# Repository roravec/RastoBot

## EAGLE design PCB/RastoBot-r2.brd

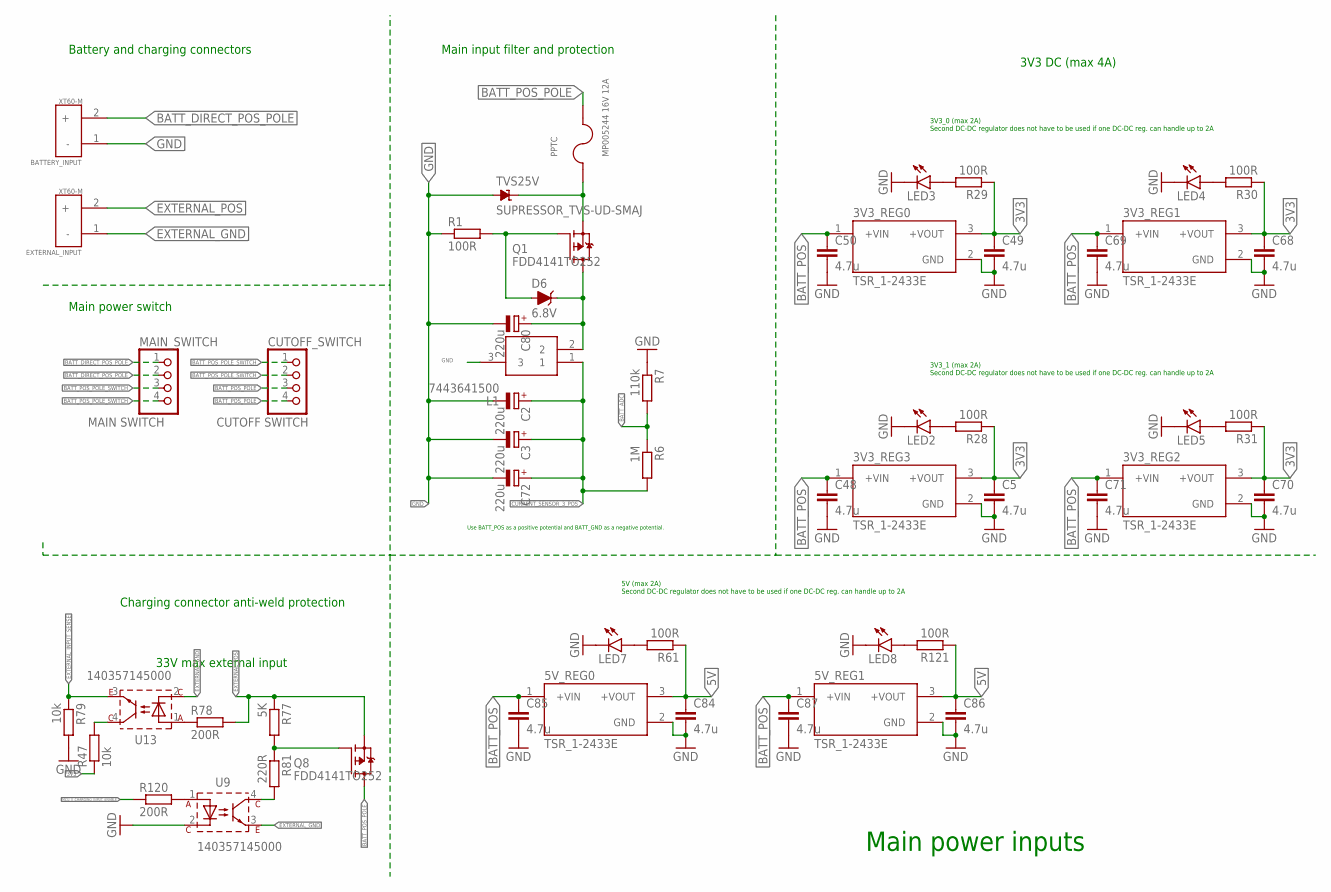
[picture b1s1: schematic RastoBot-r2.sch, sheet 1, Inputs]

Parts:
3V3_REG0, 3V3_REG1, 3V3_REG2, 3V3_REG3, 5V_REG0, 5V_REG1: TSR_1-2433E; CONV_TSR_1-2433E
BATTERY_INPUT: XT60-M; AMASS_XT60-M
C2, C3, C72, C80: 220u; E2,5-5
C5, C48, C49, C50, C68, C69, C70, C71, C84, C85, C86, C87: 4.7u; C1206
CUTOFF_SWITCH: CUTOFF SWITCH; 1X04
D6: 6.8V; SOD-323
EXTERNAL_INPUT: XT60-M; AMASS_XT60-M
L1: 7443641500; 74436413300
LED2, LED3, LED4, LED5, LED7, LED8: LEDSML0805; SML0805
MAIN_SWITCH: MAIN SWITCH; 1X04
PPTC: MP005244 16V 12A; FUSE_0ZCF0075AF2C
Q1, Q8: FDD4141TO252; TO252
R1: 100R; R0805
R6: 1M; R0805
R7: 110k; R0805
R28, R29, R30, R31, R61, R121: 100R; R0603
R47, R79: 10k; R0805
R77: 5K; R0805
R78, R120: 200R; R0805
R81: 220R; R0805
TVS25V: SUPRESSOR_TVS-UD-SMAJ; SUPRESSOR_SMAJ
U9, U13: 140357145000; WL-OCPT_SOP4

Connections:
3V3: 3V3_REG0.3 (+VOUT), 3V3_REG1.3 (+VOUT), 3V3_REG2.3 (+VOUT), 3V3_REG3.3 (+VOUT), C5.1, C49.1, C68.1, C70.1, R28.1, R29.1, R30.1, R31.1, R47.1; also elsewhere on the board
5V: 5V_REG0.3 (+VOUT), 5V_REG1.3 (+VOUT), C84.1, C86.1, R61.1, R121.1; also elsewhere on the board
BATT_ADC: R6.1, R7.2; also elsewhere on the board
BATT_DIRECT_POS_POLE: BATTERY_INPUT.2 (+), MAIN_SWITCH.1, MAIN_SWITCH.2; also elsewhere on the board
BATT_POS: 3V3_REG0.1 (+VIN), 3V3_REG1.1 (+VIN), 3V3_REG2.1 (+VIN), 3V3_REG3.1 (+VIN), 5V_REG0.1 (+VIN), 5V_REG1.1 (+VIN), C48.1, C50.1, C69.1, C71.1, C85.1, C87.1; also elsewhere on the board
BATT_POS_POLE: CUTOFF_SWITCH.3, CUTOFF_SWITCH.4, PPTC.2, Q8.3 (D)
BATT_POS_POLE_SWITCH: CUTOFF_SWITCH.1, CUTOFF_SWITCH.2, MAIN_SWITCH.3, MAIN_SWITCH.4
CURRENT_SENSOR_3_POS: C2.+, C3.+, C72.+, L1.1, R6.2; also elsewhere on the board
EXTERNAL_GND: EXTERNAL_INPUT.1 (-), U9.3, U13.2
EXTERNAL_INPUT_SENSE: R79.1, U13.3; also elsewhere on the board
EXTERNAL_POS: EXTERNAL_INPUT.2 (+), Q8.2 (S), R77.1, R78.2
GND: 3V3_REG0.2 (GND), 3V3_REG1.2 (GND), 3V3_REG2.2 (GND), 3V3_REG3.2 (GND), 5V_REG0.2 (GND), 5V_REG1.2 (GND), BATTERY_INPUT.1 (-), C2.-, C3.-, C5.2, C48.2, C49.2, C50.2, C68.2, C69.2, C70.2, C71.2, C72.-, C80.-, C84.2, C85.2, C86.2, C87.2, L1.3, LED2.C, LED3.C, LED4.C, LED5.C, LED7.C, LED8.C, R1.1, R7.1, R79.2, TVS25V.A, U9.2; also elsewhere on the board
MCU_0_CHARGING_INPUT_ENABLE: R120.1; also elsewhere on the board
unnamed: D6.A, Q1.1 (G), R1.2
unnamed: C80.+, D6.C, L1.2, Q1.3 (D)
unnamed: PPTC.1, Q1.2 (S), TVS25V.C
unnamed: LED2.A, R28.2
unnamed: LED3.A, R29.2
unnamed: LED4.A, R30.2
unnamed: LED5.A, R31.2
unnamed: R120.2, U9.1
unnamed: Q8.1 (G), R77.2, R81.1
unnamed: R81.2, U9.4
unnamed: R47.2, U13.4
unnamed: LED7.A, R61.2
unnamed: LED8.A, R121.2
unnamed: R78.1, U13.1

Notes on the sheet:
33V max external input
Charging connector anti-weld protection
Use BATT_POS as a positive potential and BATT_GND as a negative potential.
Main power inputs
3V3 DC (max 4A)
3V3_0 (max 2A) Second DC-DC regulator does not have to be used if one DC-DC reg. can handle up to 2A
3V3_1 (max 2A) Second DC-DC regulator does not have to be used if one DC-DC reg. can handle up to 2A
Main input filter and protection
Battery and charging connectors
Main power switch
5V (max 2A) Second DC-DC regulator does not have to be used if one DC-DC reg. can handle up to 2A

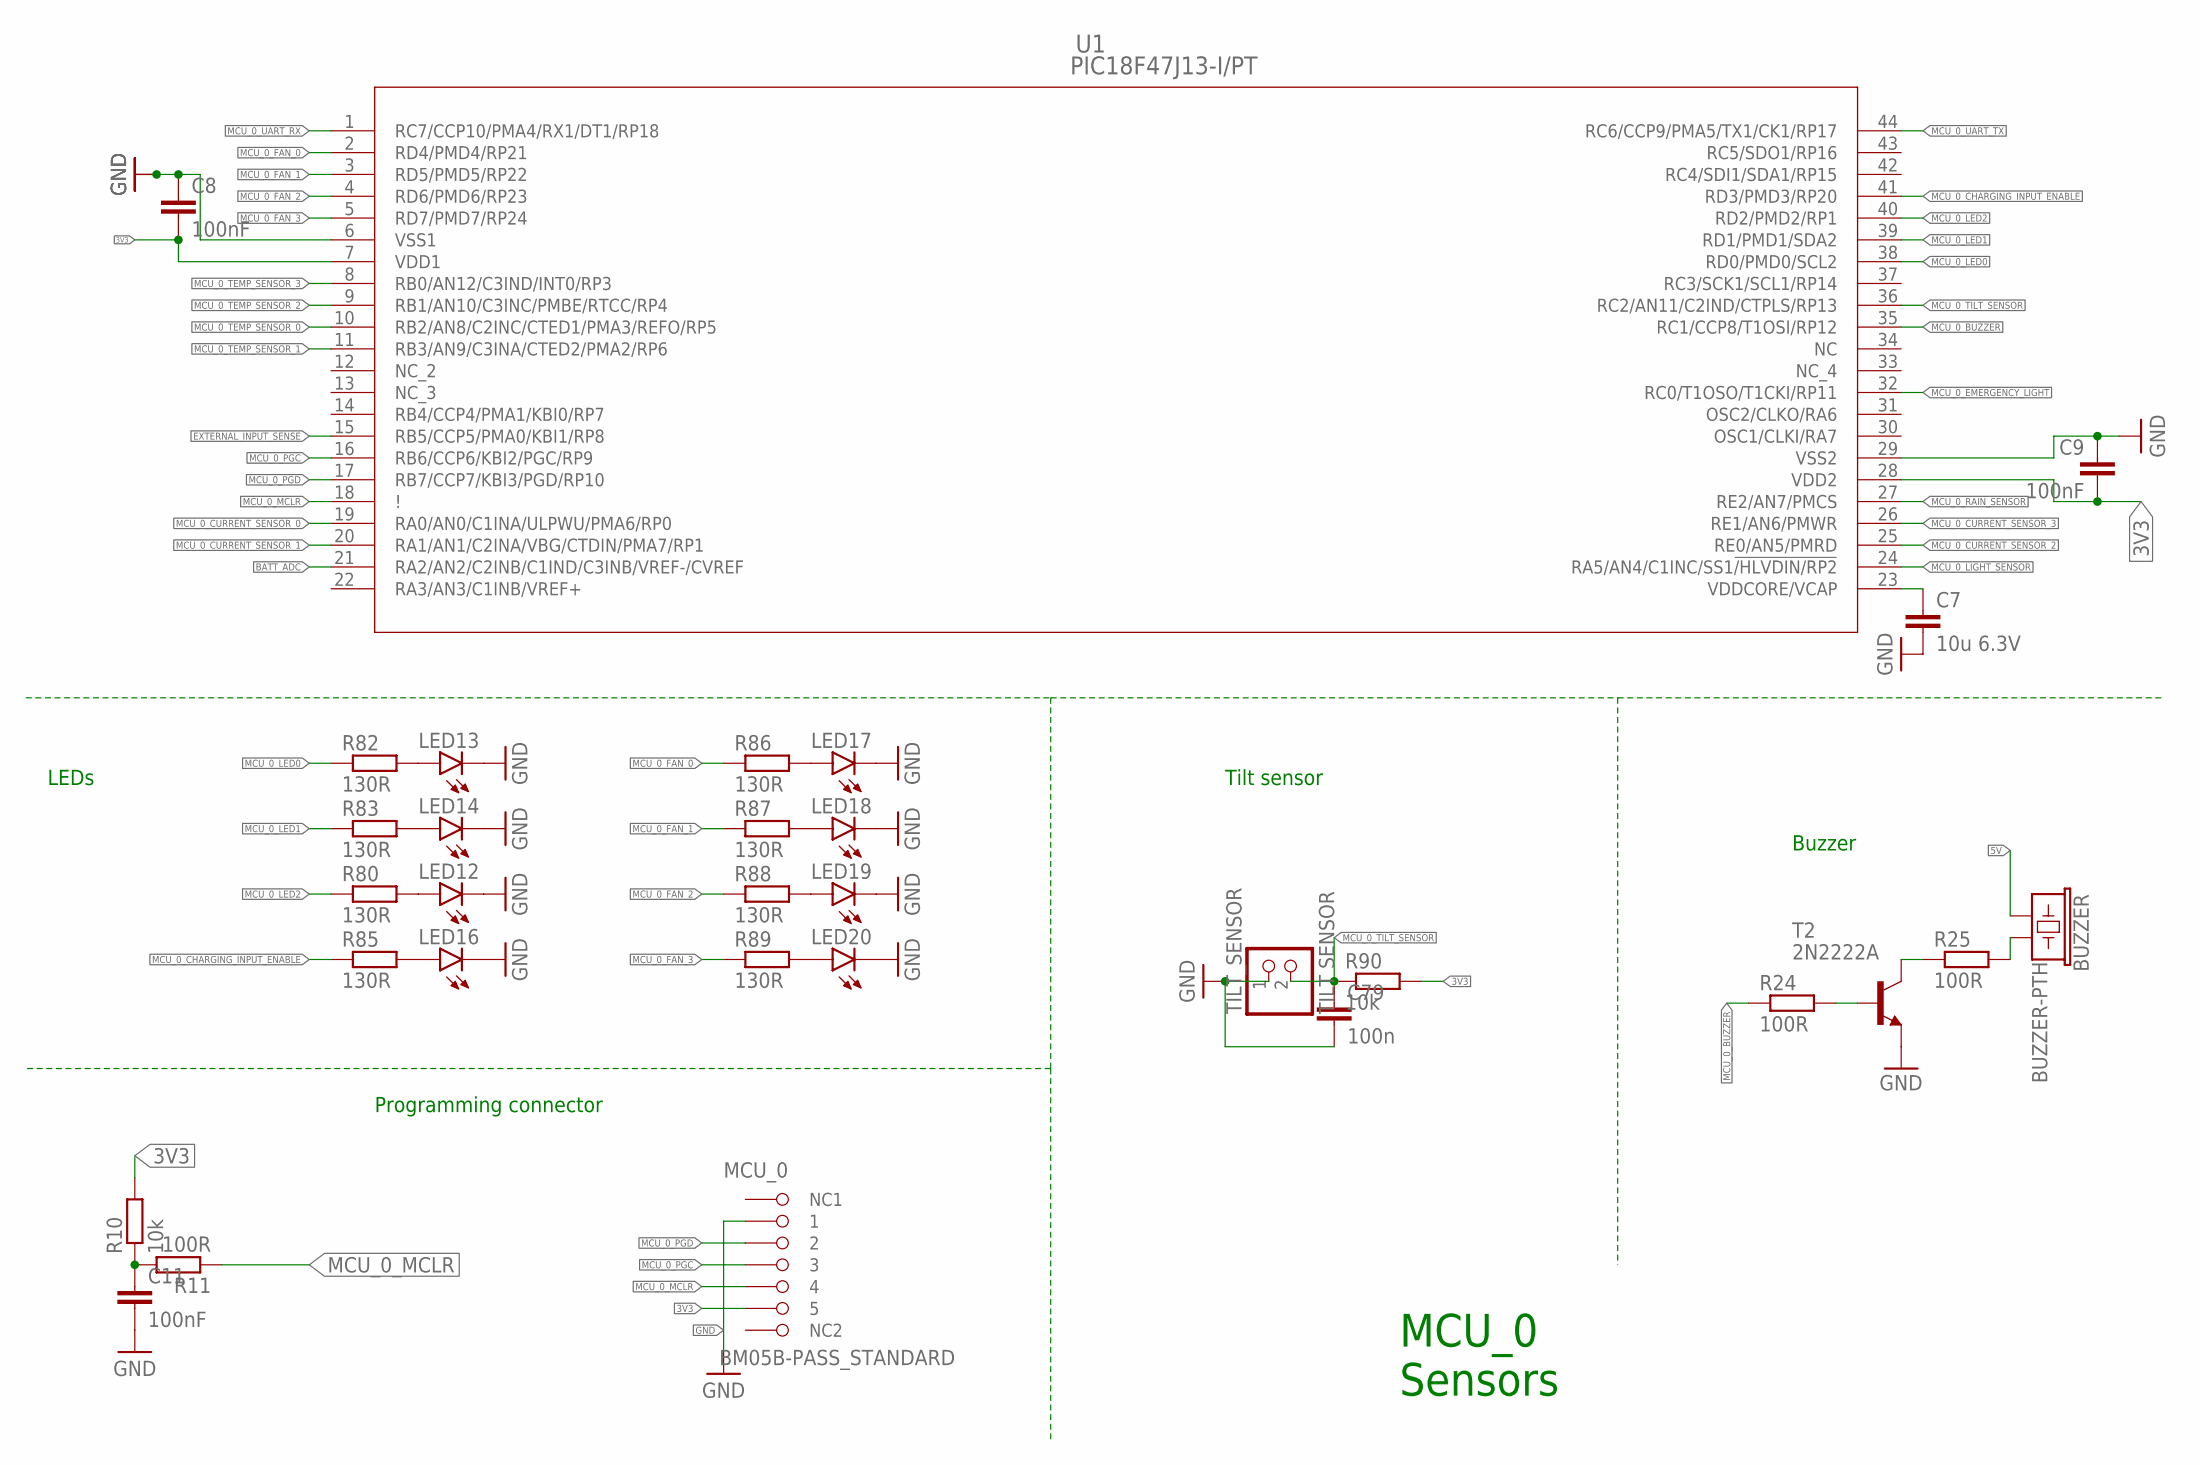
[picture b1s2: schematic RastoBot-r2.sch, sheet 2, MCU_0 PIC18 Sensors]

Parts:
BUZZER: BUZZER-PTH; BUZZER-12MM
C7: 10u 6.3V; C1206
C8, C9, C11: 100nF; C0603
C79: 100n; C1206
LED12, LED13, LED14, LED16, LED17, LED18, LED19, LED20: LEDSML0805; SML0805
MCU_0: BM05B-PASS_STANDARD; BM05B-PASS
R10: 10k; R0805
R11, R24, R25: 100R; R0805
R80, R82, R83, R85, R86, R87, R88, R89: 130R; R0603
R90: 10k; R0603
T2: 2N2222A; TO92-CBE
TILT_SENSOR: TILT SENSOR; 1X02
U1: PIC18F47J13-I/PT; TQFP44_10X10MC_MCH

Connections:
3V3: C8.2, C9.2, MCU_0.P$5 (5), R10.2, R90.2, U1.7 (VDD1), U1.28 (VDD2); also elsewhere on the board
5V: BUZZER.+ (1); also elsewhere on the board
BATT_ADC: U1.21 (RA2/AN2/C2INB/C1IND/C3INB/VREF-/CVREF); also elsewhere on the board
EXTERNAL_INPUT_SENSE: U1.15 (RB5/CCP5/PMA0/KBI1/RP8); also elsewhere on the board
GND: C7.2, C8.1, C9.1, C11.2, C79.2, LED12.C, LED13.C, LED14.C, LED16.C, LED17.C, LED18.C, LED19.C, LED20.C, MCU_0.P$1 (1), T2.E, TILT_SENSOR.1, U1.6 (VSS1), U1.29 (VSS2); also elsewhere on the board
MCU_0_BUZZER: R24.1, U1.35 (RC1/CCP8/T1OSI/RP12)
MCU_0_CHARGING_INPUT_ENABLE: R85.1, U1.41 (RD3/PMD3/RP20); also elsewhere on the board
MCU_0_CURRENT_SENSOR_0: U1.19 (RA0/AN0/C1INA/ULPWU/PMA6/RP0); also elsewhere on the board
MCU_0_CURRENT_SENSOR_1: U1.20 (RA1/AN1/C2INA/VBG/CTDIN/PMA7/RP1); also elsewhere on the board
MCU_0_CURRENT_SENSOR_2: U1.25 (RE0/AN5/PMRD); also elsewhere on the board
MCU_0_CURRENT_SENSOR_3: U1.26 (RE1/AN6/PMWR); also elsewhere on the board
MCU_0_EMERGENCY_LIGHT: U1.32 (RC0/T1OSO/T1CKI/RP11); also elsewhere on the board
MCU_0_FAN_0: R86.1, U1.2 (RD4/PMD4/RP21); also elsewhere on the board
MCU_0_FAN_1: R87.1, U1.3 (RD5/PMD5/RP22); also elsewhere on the board
MCU_0_FAN_2: R88.1, U1.4 (RD6/PMD6/RP23); also elsewhere on the board
MCU_0_FAN_3: R89.1, U1.5 (RD7/PMD7/RP24); also elsewhere on the board
MCU_0_LED0: R82.1, U1.38 (RD0/PMD0/SCL2)
MCU_0_LED1: R83.1, U1.39 (RD1/PMD1/SDA2)
MCU_0_LED2: R80.1, U1.40 (RD2/PMD2/RP1)
MCU_0_LIGHT_SENSOR: U1.24 (RA5/AN4/C1INC/SS1!/HLVDIN/RP2); also elsewhere on the board
MCU_0_MCLR: MCU_0.P$4 (4), R11.1, U1.18 (!)
MCU_0_PGC: MCU_0.P$3 (3), U1.16 (RB6/CCP6/KBI2/PGC/RP9)
MCU_0_PGD: MCU_0.P$2 (2), U1.17 (RB7/CCP7/KBI3/PGD/RP10)
MCU_0_RAIN_SENSOR: U1.27 (RE2/AN7/PMCS); also elsewhere on the board
MCU_0_TEMP_SENSOR_0: U1.10 (RB2/AN8/C2INC/CTED1/PMA3/REFO/RP5); also elsewhere on the board
MCU_0_TEMP_SENSOR_1: U1.11 (RB3/AN9/C3INA/CTED2/PMA2/RP6); also elsewhere on the board
MCU_0_TEMP_SENSOR_2: U1.9 (RB1/AN10/C3INC/PMBE/RTCC/RP4); also elsewhere on the board
MCU_0_TEMP_SENSOR_3: U1.8 (RB0/AN12/C3IND/INT0/RP3); also elsewhere on the board
MCU_0_TILT_SENSOR: C79.1, R90.1, TILT_SENSOR.2, U1.36 (RC2/AN11/C2IND/CTPLS/RP13); also elsewhere on the board
MCU_0_UART_RX: U1.1 (RC7/CCP10/PMA4/RX1/DT1/RP18); also elsewhere on the board
MCU_0_UART_TX: U1.44 (RC6/CCP9/PMA5/TX1/CK1/RP17); also elsewhere on the board
unnamed: C7.1, U1.23 (VDDCORE/VCAP)
unnamed: C11.1, R10.1, R11.2
unnamed: R24.2, T2.B
unnamed: BUZZER.- (2), R25.2
unnamed: R25.1, T2.C
unnamed: LED12.A, R80.2
unnamed: LED13.A, R82.2
unnamed: LED14.A, R83.2
unnamed: LED16.A, R85.2
unnamed: LED17.A, R86.2
unnamed: LED18.A, R87.2
unnamed: LED19.A, R88.2
unnamed: LED20.A, R89.2

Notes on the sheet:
Buzzer
MCU_0 Sensors
Tilt sensor
LEDs
Programming connector

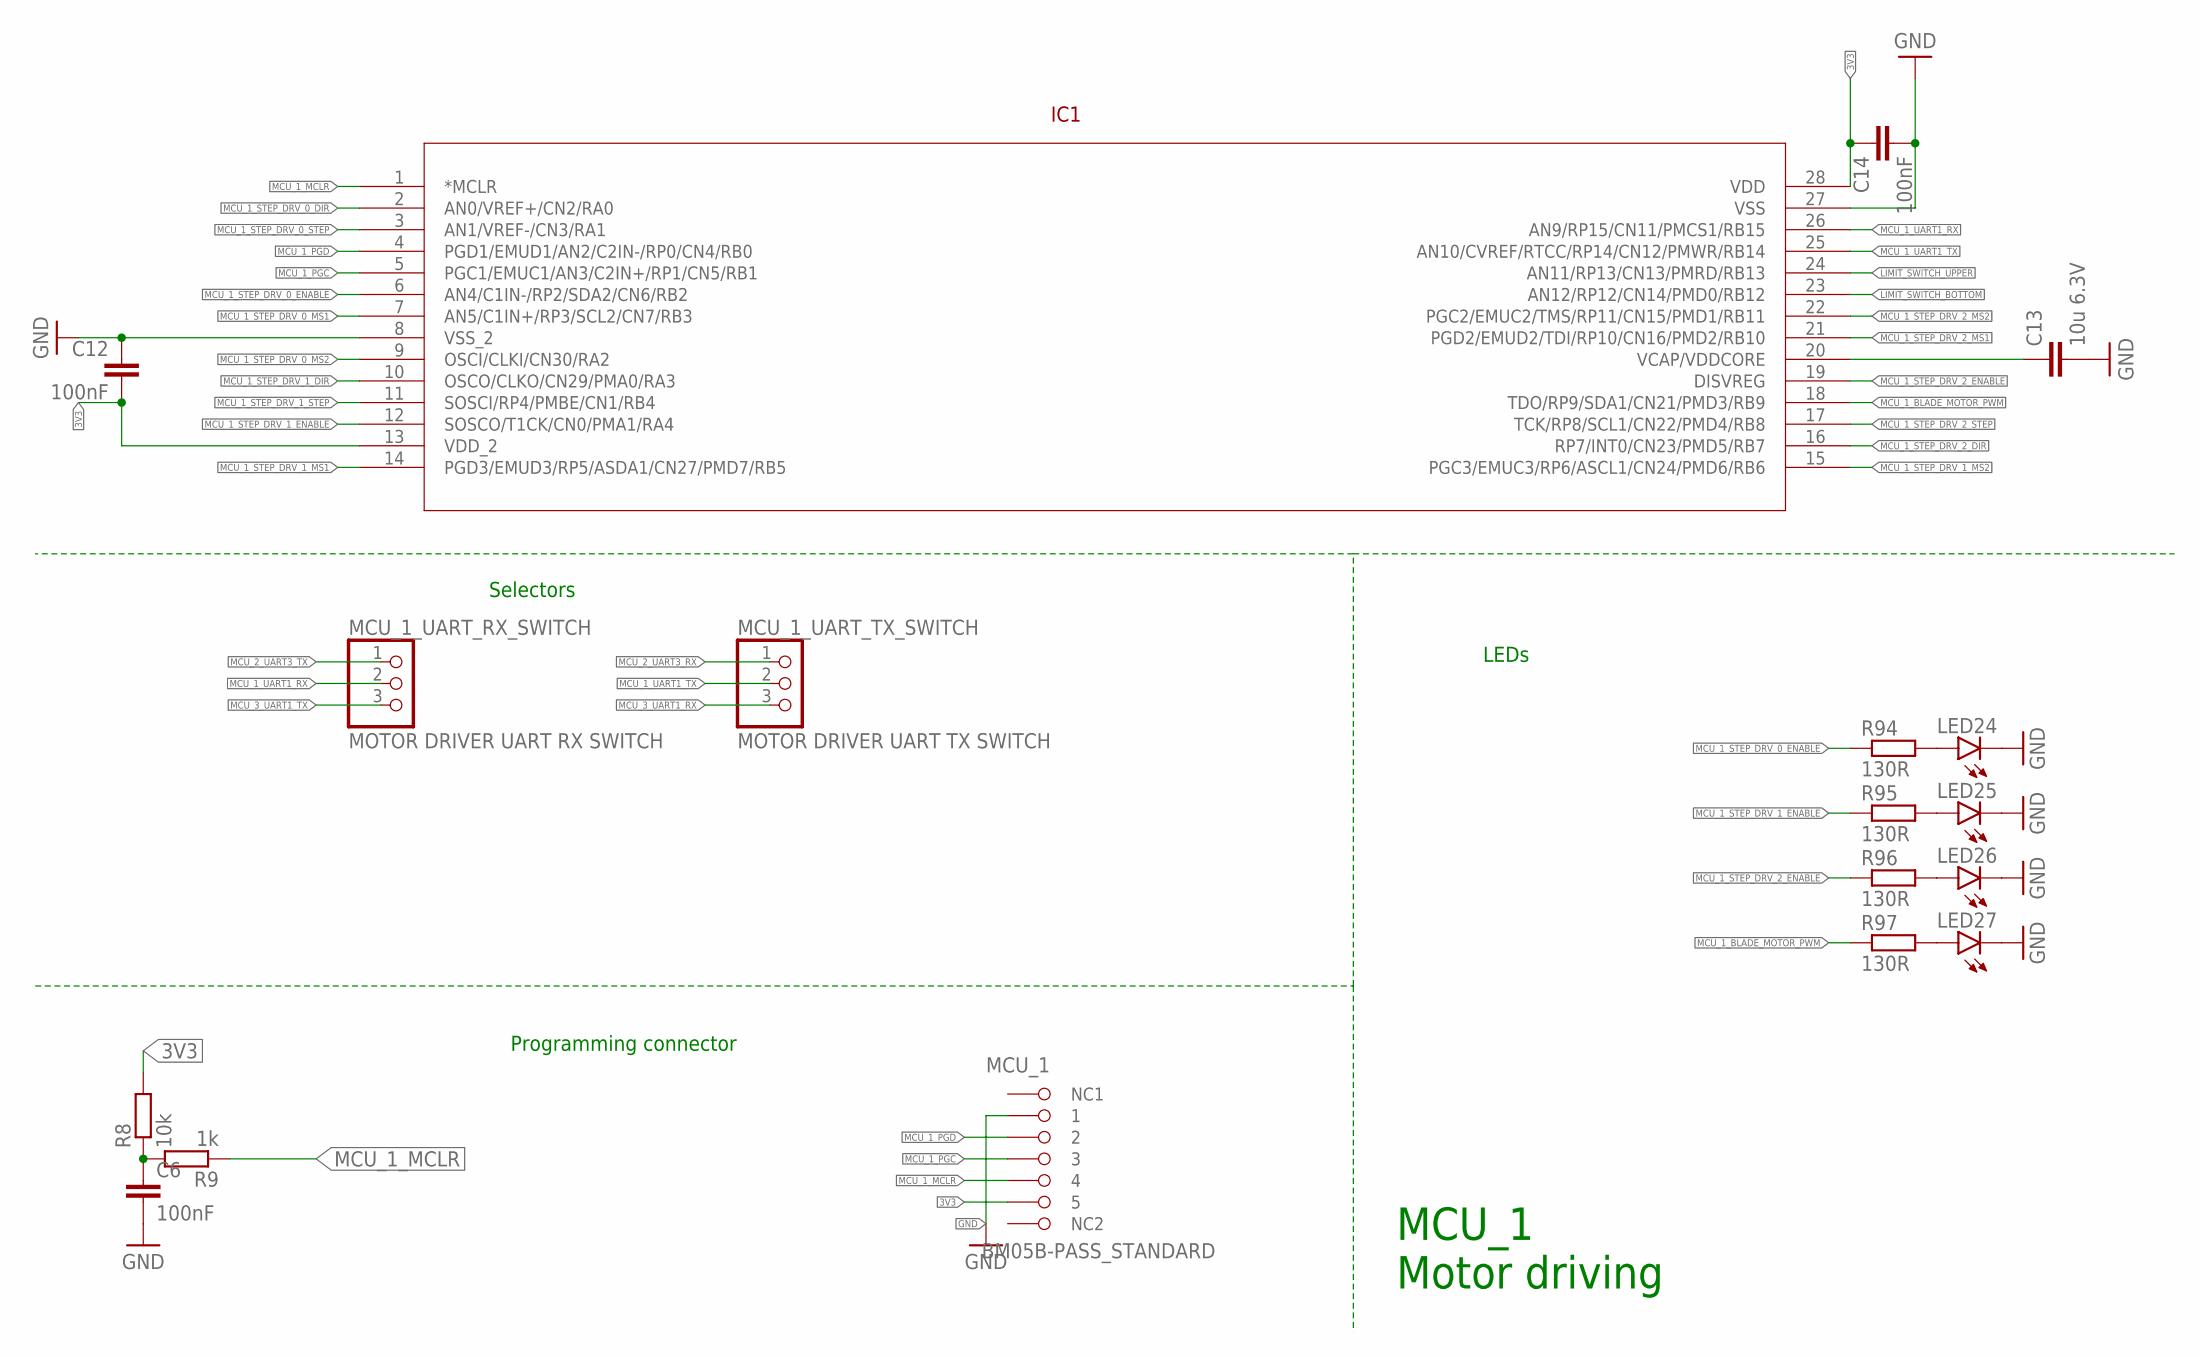
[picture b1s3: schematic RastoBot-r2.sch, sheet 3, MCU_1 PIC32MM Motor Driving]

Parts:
C6, C12, C14: 100nF; C0603
C13: 10u 6.3V; C1206
IC1: PIC24FJ32GA002-X; SPDIP28_300MC
LED24, LED25, LED26, LED27: LEDSML0805; SML0805
MCU_1: BM05B-PASS_STANDARD; BM05B-PASS
MCU_1_UART_RX_SWITCH: MOTOR DRIVER UART RX SWITCH; 1X03
MCU_1_UART_TX_SWITCH: MOTOR DRIVER UART TX SWITCH; 1X03
R8: 10k; R0805
R9: 1k; R0805
R94, R95, R96, R97: 130R; R0603

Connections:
3V3: C12.2, C14.1, IC1.13 (VDD_2), IC1.28 (VDD), MCU_1.P$5 (5), R8.2; also elsewhere on the board
GND: C6.2, C12.1, C13.2, C14.2, IC1.8 (VSS_2), IC1.27 (VSS), LED24.C, LED25.C, LED26.C, LED27.C, MCU_1.P$1 (1); also elsewhere on the board
LIMIT_SWITCH_BOTTOM: IC1.23 (AN12/RP12/CN14/PMD0/RB12); also elsewhere on the board
LIMIT_SWITCH_UPPER: IC1.24 (AN11/RP13/CN13/PMRD/RB13); also elsewhere on the board
MCU_1_BLADE_MOTOR_PWM: IC1.18 (TDO/RP9/SDA1/CN21/PMD3/RB9), R97.1; also elsewhere on the board
MCU_1_MCLR: IC1.1 (*MCLR), MCU_1.P$4 (4), R9.1
MCU_1_PGC: IC1.5 (PGC1/EMUC1/AN3/C2IN+/RP1/CN5/RB1), MCU_1.P$3 (3)
MCU_1_PGD: IC1.4 (PGD1/EMUD1/AN2/C2IN-/RP0/CN4/RB0), MCU_1.P$2 (2)
MCU_1_STEP_DRV_0_DIR: IC1.2 (AN0/VREF+/CN2/RA0); also elsewhere on the board
MCU_1_STEP_DRV_0_ENABLE: IC1.6 (AN4/C1IN-/RP2/SDA2/CN6/RB2), R94.1; also elsewhere on the board
MCU_1_STEP_DRV_0_MS1: IC1.7 (AN5/C1IN+/RP3/SCL2/CN7/RB3); also elsewhere on the board
MCU_1_STEP_DRV_0_MS2: IC1.9 (OSCI/CLKI/CN30/RA2); also elsewhere on the board
MCU_1_STEP_DRV_0_STEP: IC1.3 (AN1/VREF-/CN3/RA1); also elsewhere on the board
MCU_1_STEP_DRV_1_DIR: IC1.10 (OSCO/CLKO/CN29/PMA0/RA3); also elsewhere on the board
MCU_1_STEP_DRV_1_ENABLE: IC1.12 (SOSCO/T1CK/CN0/PMA1/RA4), R95.1; also elsewhere on the board
MCU_1_STEP_DRV_1_MS1: IC1.14 (PGD3/EMUD3/RP5/ASDA1/CN27/PMD7/RB5); also elsewhere on the board
MCU_1_STEP_DRV_1_MS2: IC1.15 (PGC3/EMUC3/RP6/ASCL1/CN24/PMD6/RB6); also elsewhere on the board
MCU_1_STEP_DRV_1_STEP: IC1.11 (SOSCI/RP4/PMBE/CN1/RB4); also elsewhere on the board
MCU_1_STEP_DRV_2_DIR: IC1.16 (RP7/INT0/CN23/PMD5/RB7); also elsewhere on the board
MCU_1_STEP_DRV_2_ENABLE: IC1.19 (DISVREG), R96.1; also elsewhere on the board
MCU_1_STEP_DRV_2_MS1: IC1.21 (PGD2/EMUD2/TDI/RP10/CN16/PMD2/RB10); also elsewhere on the board
MCU_1_STEP_DRV_2_MS2: IC1.22 (PGC2/EMUC2/TMS/RP11/CN15/PMD1/RB11); also elsewhere on the board
MCU_1_STEP_DRV_2_STEP: IC1.17 (TCK/RP8/SCL1/CN22/PMD4/RB8); also elsewhere on the board
MCU_1_UART1_RX: IC1.26 (AN9/RP15/CN11/PMCS1/RB15), MCU_1_UART_RX_SWITCH.2; also elsewhere on the board
MCU_1_UART1_TX: IC1.25 (AN10/CVREF/RTCC/RP14/CN12/PMWR/RB14), MCU_1_UART_TX_SWITCH.2; also elsewhere on the board
MCU_2_UART3_RX: MCU_1_UART_TX_SWITCH.1; also elsewhere on the board
MCU_2_UART3_TX: MCU_1_UART_RX_SWITCH.1; also elsewhere on the board
MCU_3_UART1_RX: MCU_1_UART_TX_SWITCH.3; also elsewhere on the board
MCU_3_UART1_TX: MCU_1_UART_RX_SWITCH.3; also elsewhere on the board
unnamed: C6.1, R8.1, R9.2
unnamed: C13.1, IC1.20 (VCAP/VDDCORE)
unnamed: LED24.A, R94.2
unnamed: LED25.A, R95.2
unnamed: LED26.A, R96.2
unnamed: LED27.A, R97.2

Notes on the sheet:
MCU_1 Motor driving
LEDs
Programming connector
Selectors

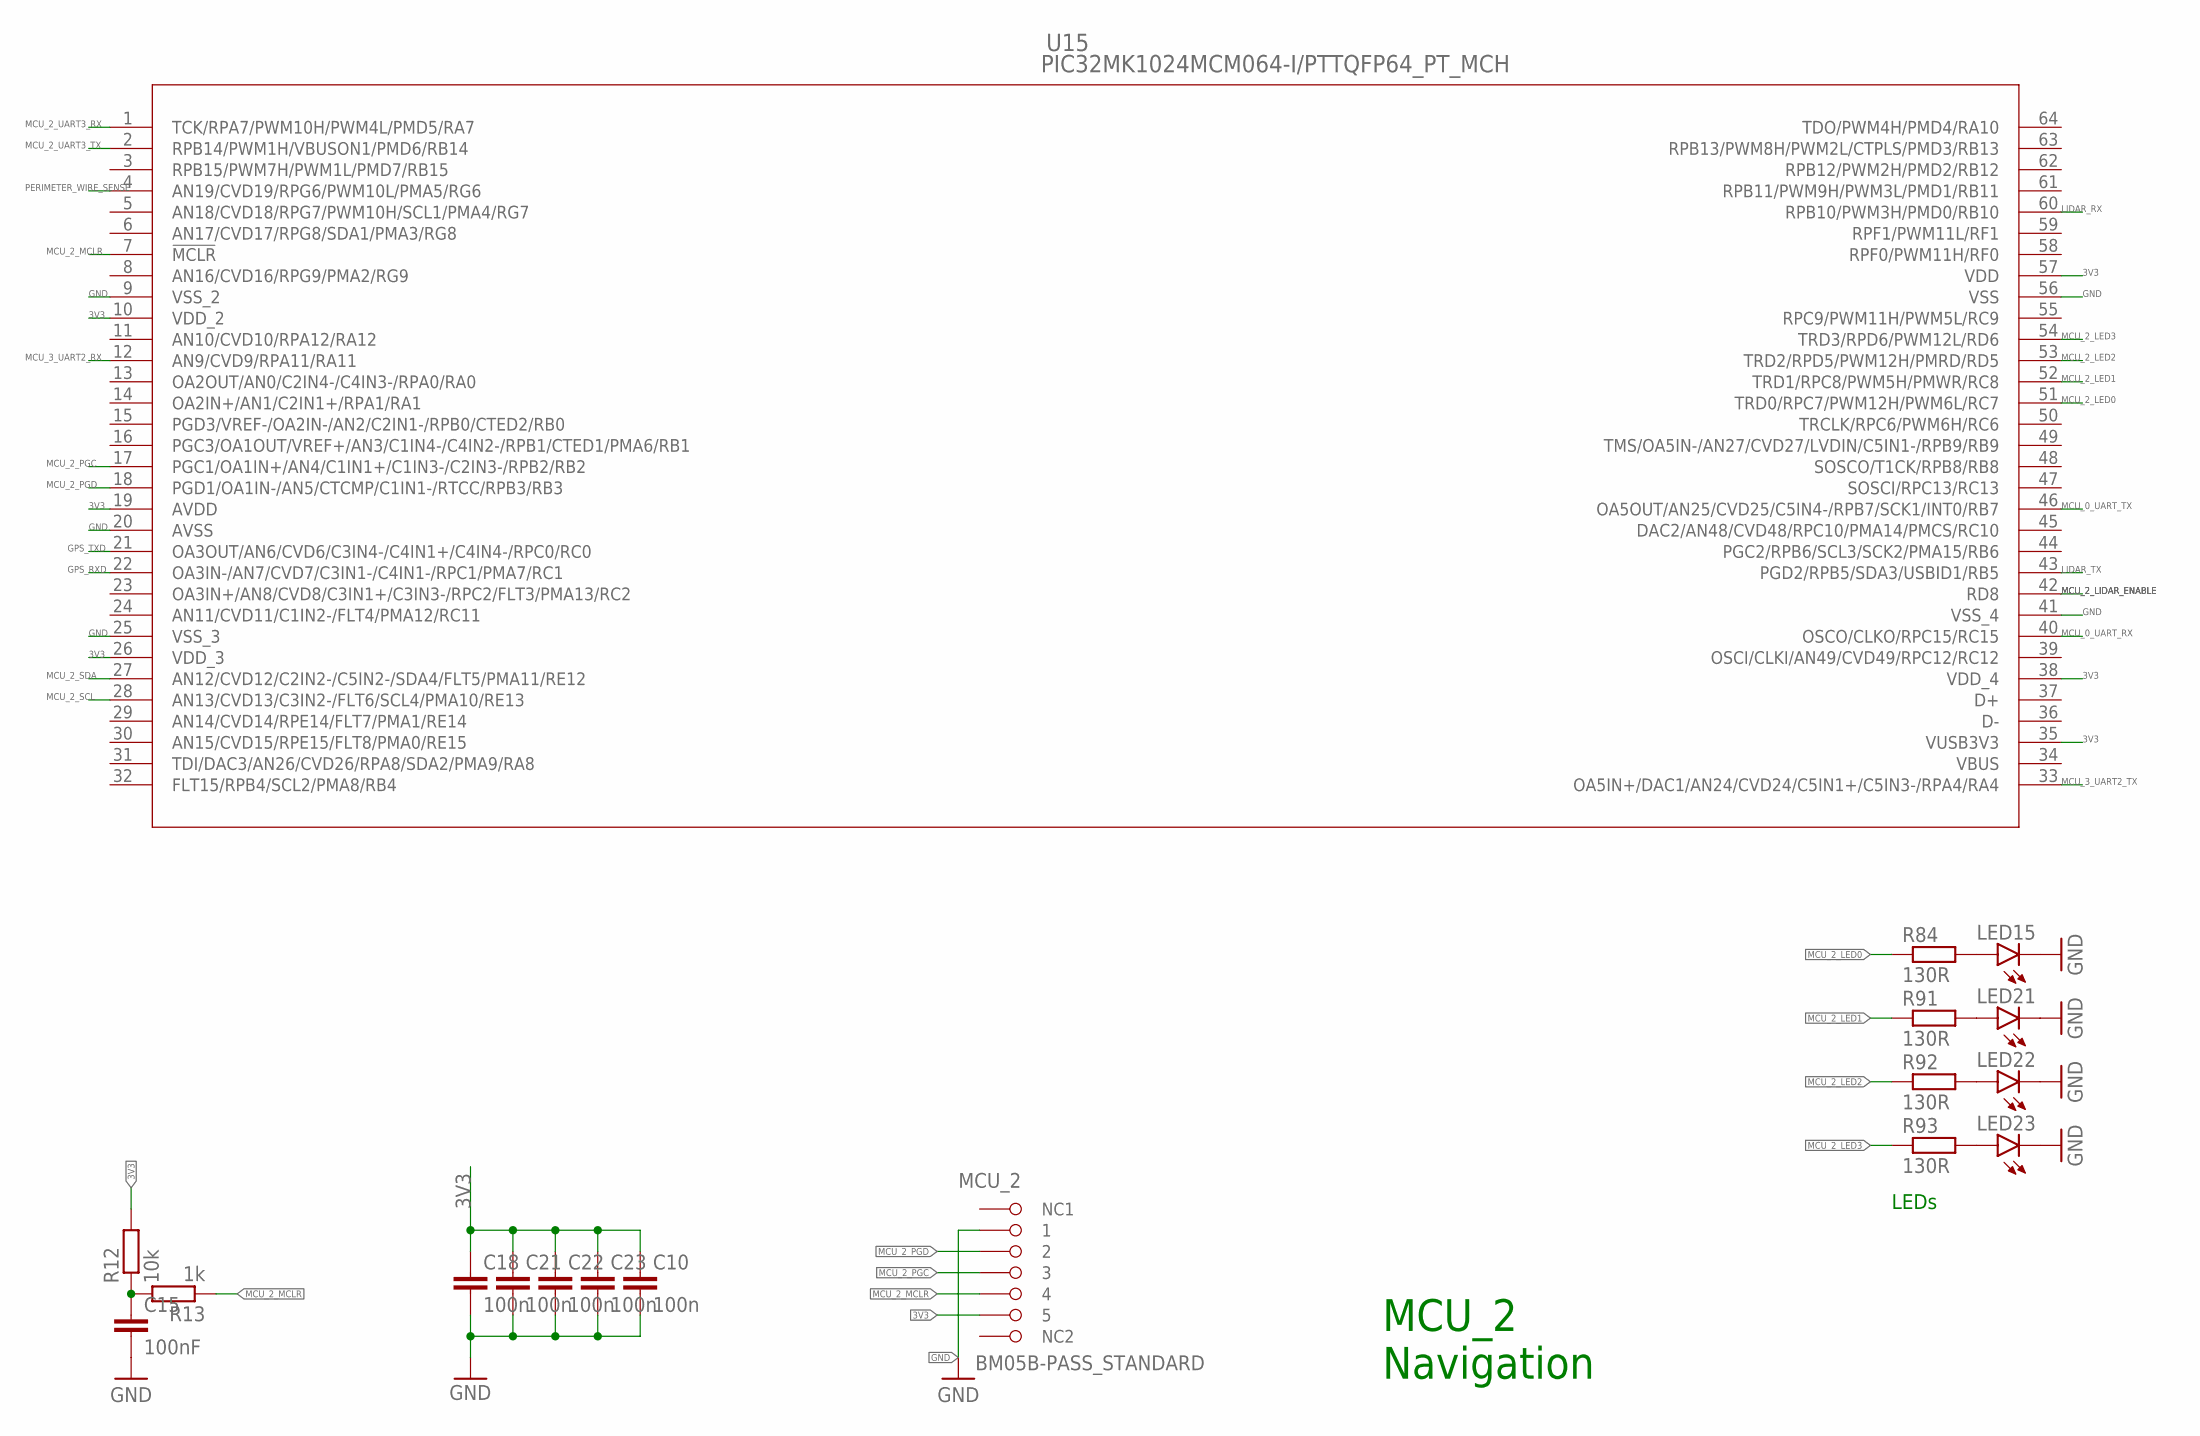
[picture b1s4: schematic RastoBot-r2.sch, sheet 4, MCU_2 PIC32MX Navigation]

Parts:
C10, C18, C21, C22, C23: 100n; C0603
C15: 100nF; C0603
LED15, LED21, LED22, LED23: LEDSML0805; SML0805
MCU_2: BM05B-PASS_STANDARD; BM05B-PASS
R12: 10k; R0805
R13: 1k; R0805
R84, R91, R92, R93: 130R; R0603
U15: PIC32MK1024MCM064-I/PTTQFP64_PT_MCH; TQFP64_PT_MCH

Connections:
3V3: C10.1, C18.1, C21.1, C22.1, C23.1, MCU_2.P$5 (5), R12.2, U15.10 (VDD_2), U15.19 (AVDD), U15.26 (VDD_3), U15.35 (VUSB3V3), U15.38 (VDD_4), U15.57 (VDD); also elsewhere on the board
GND: C10.2, C15.2, C18.2, C21.2, C22.2, C23.2, LED15.C, LED21.C, LED22.C, LED23.C, MCU_2.P$1 (1), U15.9 (VSS_2), U15.20 (AVSS), U15.25 (VSS_3), U15.41 (VSS_4), U15.56 (VSS); also elsewhere on the board
GPS_RXD: U15.22 (OA3IN-/AN7/CVD7/C3IN1-/C4IN1-/RPC1/PMA7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); also elsewhere on the board
GPS_TXD: U15.21 (OA3OUT/AN6/CVD6/C3IN4-/C4IN1+/C4IN4-/RP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); also elsewhere on the board
LIDAR_RX: U15.60 (RPB10/PWM3H/PMD0/RB10); also elsewhere on the board
LIDAR_TX: U15.43 (PGD2/RPB5/SDA3/USBID1/RB5); also elsewhere on the board
MCU_0_UART_RX: U15.40 (OSCO/CLKO/RPC15/RC15); also elsewhere on the board
MCU_0_UART_TX: U15.46 (OA5OUT/AN25/CVD25/C5IN4-/RPB7/SCK1/INT0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); also elsewhere on the board
MCU_2_LED0: R84.1, U15.51 (TRD0/RPC7/PWM12H/PWM6L/RC7)
MCU_2_LED1: R91.1, U15.52 (TRD1/RPC8/PWM5H/PMWR/RC8)
MCU_2_LED2: R92.1, U15.53 (TRD2/RPD5/PWM12H/PMRD/RD5)
MCU_2_LED3: R93.1, U15.54 (TRD3/RPD6/PWM12L/RD6)
MCU_2_LIDAR_ENABLE: U15.42 (RD8); also elsewhere on the board
MCU_2_MCLR: MCU_2.P$4 (4), R13.1, U15.7 (!MCLR)
MCU_2_PGC: MCU_2.P$3 (3), U15.17 (PGC1/OA1IN+/AN4/C1IN1+/C1IN3-/C2IN3-/RP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)
MCU_2_PGD: MCU_2.P$2 (2), U15.18 (PGD1/OA1IN-/AN5/CTCMP/C1IN1-/RTCC/RPB3/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)
MCU_2_SCL: U15.28 (AN13/CVD13/C3IN2-/FLT6/SCL4/PMA10/RE13); also elsewhere on the board
MCU_2_SDA: U15.27 (AN12/CVD12/C2IN2-/C5IN2-/SDA4/FLT5/PMA1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); also elsewhere on the board
MCU_2_UART3_RX: U15.1 (TCK/RPA7/PWM10H/PWM4L/PMD5/RA7); also elsewhere on the board
MCU_2_UART3_TX: U15.2 (RPB14/PWM1H/VBUSON1/PMD6/RB14); also elsewhere on the board
MCU_3_UART2_RX: U15.12 (AN9/CVD9/RPA11/RA11); also elsewhere on the board
MCU_3_UART2_TX: U15.33 (OA5IN+/DAC1/AN24/CVD24/C5IN1+/C5IN3-/RP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); also elsewhere on the board
unnamed: C15.1, R12.1, R13.2
unnamed: LED15.A, R84.2
unnamed: LED21.A, R91.2
unnamed: LED22.A, R92.2
unnamed: LED23.A, R93.2
PERIMETER_WIRE_SENSE: U15.4 (AN19/CVD19/RPG6/PWM10L/PMA5/RG6); also elsewhere on the board
VBUS: U15.34 (VBUS)

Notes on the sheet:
MCU_2 Navigation
LEDs

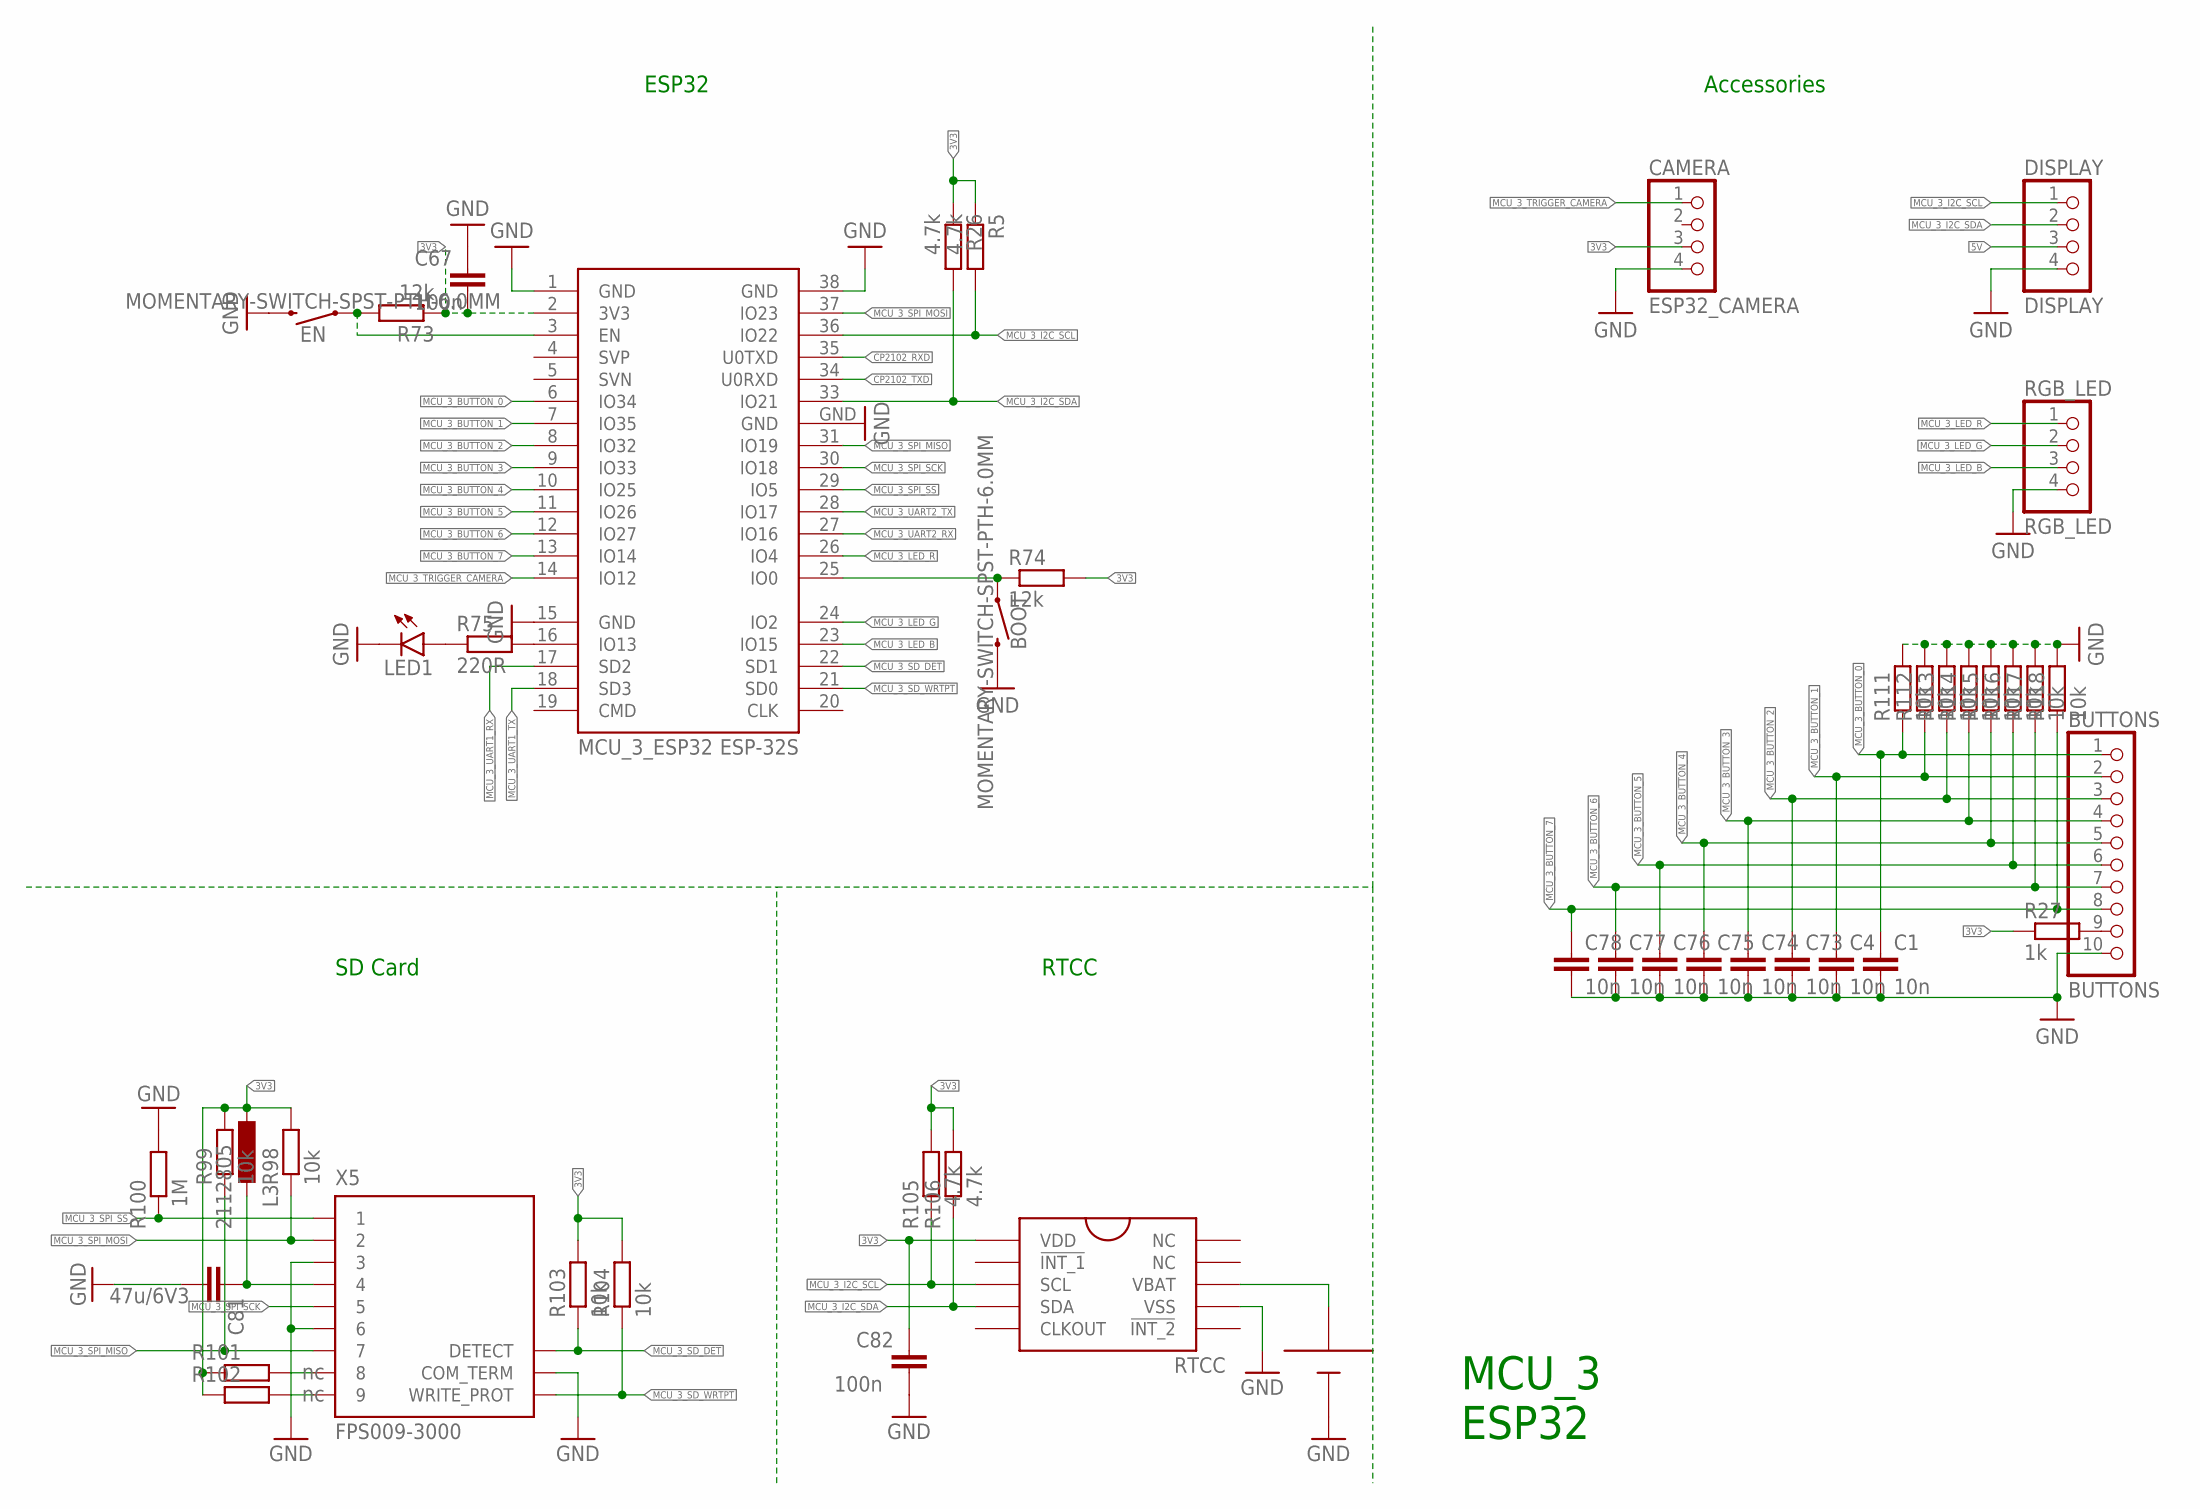
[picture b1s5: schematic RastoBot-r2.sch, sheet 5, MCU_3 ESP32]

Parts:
BATT1: SMTU2032LF
BOOT: MOMENTARY-SWITCH-SPST-PTH-6.0MM; TACTILE_SWITCH_PTH_6.0MM
BUTTONS: BUTTONS; 1X10
C1, C4, C73, C74, C75, C76, C77, C78: 10n; C0603
C67, C82: 100n; C0603
C81: 47u/6V3; C1206
CAMERA: ESP32_CAMERA; 1X04
DISPLAY: DISPLAY; 1X04
EN: MOMENTARY-SWITCH-SPST-PTH-6.0MM; TACTILE_SWITCH_PTH_6.0MM
L3: 2112805; L2825P
LED1: LEDSML0805; SML0805
MCU_3_ESP32: ESP-32S
R5, R26, R105, R106: 4.7k; R0603
R27: 1k; R0603
R73, R74: 12k; R0805
R75: 220R; R0805
R98, R99, R103, R104, R111, R112, R113, R114, R115, R116, R117, R118: 10k; R0603
R100: 1M; R0603
R101, R102: nc; R0603
RGB_LED: RGB_LED; 1X04
RTCC: AB-RTCMC-32.768KHZ-B5ZE-S3-T
X5: FPS009-3000

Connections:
3V3: C67.2, C82.1, CAMERA.3, L3.2, MCU_3_ESP32.2 (3V3), R5.1, R26.1, R27.1, R73.1, R74.2, R98.2, R99.2, R101.1, R102.1, R103.2, R104.2, R105.2, R106.2, RTCC.1 (VDD); also elsewhere on the board
5V: DISPLAY.3; also elsewhere on the board
CP2102_RXD: MCU_3_ESP32.35 (U0TXD); also elsewhere on the board
CP2102_TXD: MCU_3_ESP32.34 (U0RXD); also elsewhere on the board
GND: BATT1.MINUS, BOOT.3 (2), BUTTONS.10, C1.2, C4.2, C67.1, C73.2, C74.2, C75.2, C76.2, C77.2, C78.2, C81.2, C82.2, CAMERA.4, DISPLAY.4, EN.3 (2), LED1.C, MCU_3_ESP32.1 (GND), MCU_3_ESP32.15 (GND), MCU_3_ESP32.38 (GND), MCU_3_ESP32.GND, R100.2, R111.2, R112.2, R113.2, R114.2, R115.2, R116.2, R117.2, R118.2, RGB_LED.4, RTCC.7 (VSS), X5.3, X5.6, X5.COM_TERM; also elsewhere on the board
MCU_3_BUTTON_0: BUTTONS.1, C1.1, MCU_3_ESP32.6 (IO34), R111.1
MCU_3_BUTTON_1: BUTTONS.2, C4.1, MCU_3_ESP32.7 (IO35), R112.1
MCU_3_BUTTON_2: BUTTONS.3, C73.1, MCU_3_ESP32.8 (IO32), R113.1
MCU_3_BUTTON_3: BUTTONS.4, C74.1, MCU_3_ESP32.9 (IO33), R114.1
MCU_3_BUTTON_4: BUTTONS.5, C75.1, MCU_3_ESP32.10 (IO25), R115.1
MCU_3_BUTTON_5: BUTTONS.6, C76.1, MCU_3_ESP32.11 (IO26), R116.1
MCU_3_BUTTON_6: BUTTONS.7, C77.1, MCU_3_ESP32.12 (IO27), R117.1
MCU_3_BUTTON_7: BUTTONS.8, C78.1, MCU_3_ESP32.13 (IO14), R118.1
MCU_3_I2C_SCL: DISPLAY.1, MCU_3_ESP32.36 (IO22), R5.2, R105.1, RTCC.3 (SCL); also elsewhere on the board
MCU_3_I2C_SDA: DISPLAY.2, MCU_3_ESP32.33 (IO21), R26.2, R106.1, RTCC.4 (SDA); also elsewhere on the board
MCU_3_LED_B: MCU_3_ESP32.23 (IO15), RGB_LED.3
MCU_3_LED_G: MCU_3_ESP32.24 (IO2), RGB_LED.2
MCU_3_LED_R: MCU_3_ESP32.26 (IO4), RGB_LED.1
MCU_3_SD_DET: MCU_3_ESP32.22 (SD1), R103.1, X5.DETECT
MCU_3_SD_WRTPT: MCU_3_ESP32.21 (SD0), R104.1, X5.WRITE_PROT
MCU_3_SPI_MISO: MCU_3_ESP32.31 (IO19), R99.1, X5.7
MCU_3_SPI_MOSI: MCU_3_ESP32.37 (IO23), R98.1, X5.2
MCU_3_SPI_SCK: MCU_3_ESP32.30 (IO18), X5.5
MCU_3_SPI_SS: MCU_3_ESP32.29 (IO5), R100.1, X5.1
MCU_3_TRIGGER_CAMERA: CAMERA.1, MCU_3_ESP32.14 (IO12)
MCU_3_UART1_RX: MCU_3_ESP32.17 (SD2); also elsewhere on the board
MCU_3_UART1_TX: MCU_3_ESP32.18 (SD3); also elsewhere on the board
MCU_3_UART2_RX: MCU_3_ESP32.27 (IO16); also elsewhere on the board
MCU_3_UART2_TX: MCU_3_ESP32.28 (IO17); also elsewhere on the board
unnamed: BUTTONS.9, R27.2
unnamed: BOOT.1, MCU_3_ESP32.25 (IO0), R74.1
unnamed: EN.1, MCU_3_ESP32.3 (EN), R73.2
unnamed: MCU_3_ESP32.16 (IO13), R75.2
unnamed: LED1.A, R75.1
unnamed: R102.2, X5.9
unnamed: R101.2, X5.8
unnamed: BATT1.PLUS, RTCC.8 (VBAT)
unnamed: C81.1, L3.1, X5.4

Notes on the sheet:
SD Card
RTCC
Accessories
ESP32
MCU_3 ESP32

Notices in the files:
PCB/Production_221101/RastoBot-r1_BOM.csv:
"PIC18F47J13-I/PT";"PIC18F47J13-I/PT";"TQFP44_10X10MC_MCH";"U1";"";"";"";"";"Copyright (C) 2022 Ultra Librarian. All rights reserved.";"";"";"";"";"";"";"";"";"";"";"pic18f47j13-i/pt";"";"Microchip";"";"";"";"";"";"";"";"";"";"";"";"";"";"";"";"";"";"";"";"";
parts and their libraries:
skorra: COPYRIGHT: Copyright (C) 2022 Ultra Librarian. All rights reserved.
Wurth_Optocoupler_WL-OCPT: Copyright: Würth Elektronik
SparkFun-Switches: Licensing: Creative Commons ShareAlike 4.0 International - https://creativecommons.org/licenses/by-sa/4.0
